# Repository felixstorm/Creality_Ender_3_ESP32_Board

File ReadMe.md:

# ESP32 RepRap Controller Board for Creality Ender 3

**Use at your own risk! This is just a personal project and work in progress, and I do not have any professional experience in this field. And although it does work nicely for me, the power supply and heaters have enough power to set your house on fire if not used correctly. Therefore be sure to think about the stuff you do yourself and respect all the necessary safety precautions!**

This is a bare minimum RepRap mainboard that I created for my own Creality Ender 3, heavily based on the work of [Simon Jouet](https://github.com/simon-jouet).  
He did a great job developing the HAL for the ESP32 for [Marlin](https://github.com/MarlinFirmware/Marlin/tree/bugfix-2.0.x/Marlin/src/HAL/HAL_ESP32) including the use of I2S and shift registers to drive the stepper drivers. I2S needs very little hardware overhead, but increases the somewhat limited number of GPIOs on the ESP32 significantly, allowing to also connect the stock Ender 3 display as well as a BLTouch and also parts cooling, control board and hotend fans independently. Additionally it provides perfect stepper timing (based on the ESP32's internal I2S clock).  
He also developed his own [ESP32 controller](https://github.com/simon-jouet/ESP32Controller) which this board is heavily based on.

This is the third iteration of the board, and although it has only been in use for a few hours yet, it does seem to work nicely in every respect. Will post updates here...

## Technical Notes
* The board is the bare minimum to help my Ender 3 to a 32 bit brain and WiFi. I use breakout boards wherever it makes sense to reduce complexity as much as possible. It is not primarly geared towards low cost, but towards little effort (although it took more of it than I hoped for in the beginning ;-) ).
* The board is through hole and single sided with a few wire bridges. This is because I am so old that I am more used to THT than SMD, because most stuff is on on breakout boards anyway and because I wanted to mill the board on my CNC.
* There is a [PDF](https://github.com/felixstorm/Creality_Ender_3_ESP32_Board/blob/master/201904_Esp32ReprapController_Schematic_and_Layout.pdf) with schematic and board layout and a [photo of my board](https://github.com/felixstorm/Creality_Ender_3_ESP32_Board/blob/master/Creality_Ender_3_ESP32_Board.jpg) available to get a quick look.
* The board is larger (100 x 160 mm) than the stock Ender 3 mainboard, so you will need (to print) a different case for it. I will probably develop one some time, put it on Thingiverse and then link it from here.
* SD card reader: I am using a microSD to regular SD extension and have the SD card reader mounted behind the display, so I used a microSD breakout board with the slot oriented inwards where I just plug in the extension cable. The board used to be 5V, but I shorted the voltage regulator with some solder to make it work with 3.3V.
* Stepper Drivers: I use TMC2208 because they are quiet and relatively cheap. Since I am not interested in any tuning here, I hard-wired it's configuration pins. In case you want to use different drivers, you might have to cut traces on these pins or change the layout.
* I have yet to make use of WiFi. My plan is to use [ESP3D](https://github.com/luc-github/ESP3D) with Marlin integrated at some point in time, but I have yet to figure out how far Luc as gotten with the integration of ESP3 into [Marlin](https://github.com/luc-github/Marlin/tree/bugfix-2.0.x).
* The board should run stock [Marlin for ESP32](https://github.com/MarlinFirmware/Marlin/tree/bugfix-2.0.x/Marlin/src/HAL/HAL_ESP32) (as my minor pull requests have all been merged now). For reference, my current personal setup including my complete configuration is available [here](https://github.com/felixstorm/Marlin/tree/Felix_Ender3_ESP32_2.0.x).
* In case you create your own board / layout, be sure to take special care of the I2S lines. The first two variants of my board also did work somehow, but the temperature readings were really, really noisy (jumping up and down wildly by 5-8 °C). It turned out that this was caused by my really poor routing of the I2S lines which injected lots of noise into VCC. The second iteration was better, but there was still more noise than I had hoped for, so I took more time for the layout of board revision r3, moved components and switched pins to separate I2S far from VCC and analog pins and to reduce the complexity of the layout, routed all power and analog lines by hand, placed a ground plane around the I2S lines and left only standard digital lines for the auto-router.
* I used [KiCad](http://www.kicad.org/) for the schematic and the board and [TopoR Lite](https://www.eremex.com/products/topor/) for auto-routing. TopoR works quite well, is available for free with some (totally acceptable) limitations and was pretty helpful as it also has a special single-sided mode, even though it took some time to get used to.
* For milling, I used [pcb2gcode](https://github.com/pcb2gcode/pcb2gcode), which also worked well for me since it allows to add safety margins easily by setting a cutter width larger than the actual cutter. It will still mill between traces that are closer together than theoretically possible with the specified cutter width (which [FlatCAM](http://flatcam.org/) unfortunately does not do), but leaves all other traces wider. And although it is command-line only, one can put all settings in a config file per project and it does dump out nice SVG files where it illustrates its calculations.

## License: MIT

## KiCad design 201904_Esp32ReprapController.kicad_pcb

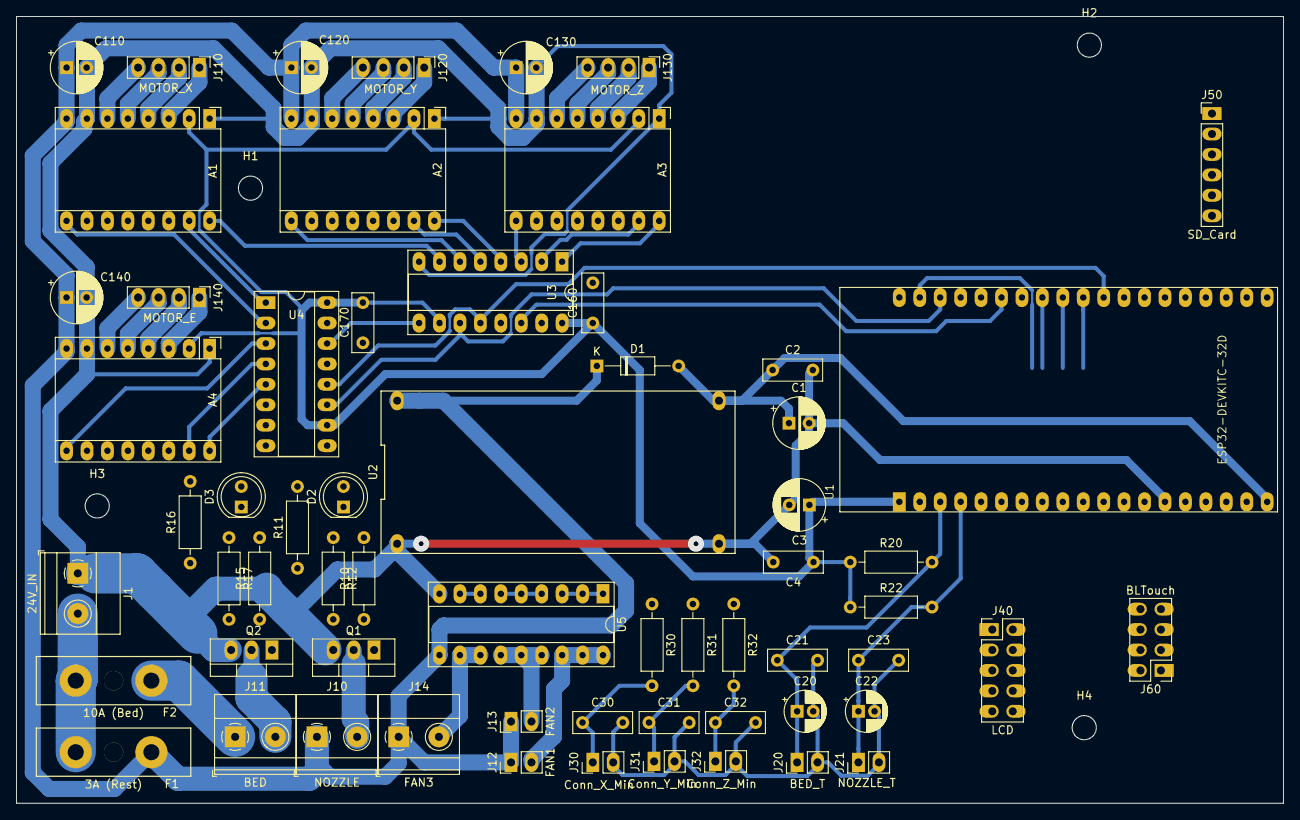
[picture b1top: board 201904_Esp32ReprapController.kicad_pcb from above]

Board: 2 copper layers, 157.5 x 97.8 mm, 66 parts (0 on the bottom side), 68 nets.

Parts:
A1: DRIVER_X; Pololu_Breakout-16_15.2x20.3mm_LongPads
A2: DRIVER_Y; Pololu_Breakout-16_15.2x20.3mm_LongPads
A3: DRIVER_Z; Pololu_Breakout-16_15.2x20.3mm_LongPads
A4: DRIVER_E; Pololu_Breakout-16_15.2x20.3mm_LongPads
C1, C3, C110, C120, C130, C140: 100uF; CP_Radial_D6.3mm_P2.50mm
C2, C4, C21, C23, C30, C31, C32, C160, C170: 0.1uF; C_Rect_L7.2mm_W2.5mm_P5.00mm_FKS2_FKP2_MKS2_MKP2
C20, C22: 4.7uF; CP_Radial_D5.0mm_P2.00mm
D1: 1N5819; D_DO-35_SOD27_P10.16mm_Horizontal
D2: LED_NOZ; LED_D5.0mm
D3: LED_BED; LED_D5.0mm
F1: 3A (Rest); Fuse_ESKA_380.000
F2: 10A (Bed); Fuse_ESKA_380.000
H1, H2, H3, H4: MountingHole; MountingHole_3mm
J1: 24V_IN; TerminalBlock_ScrewTerminal_1x02_P5.00mm_Horizontal
J10: NOZZLE; TerminalBlock_ScrewTerminal_1x02_P5.00mm_Horizontal
J11: BED; TerminalBlock_ScrewTerminal_1x02_P5.00mm_Horizontal
J12: FAN1; PinHeader_1x02_P2.54mm_Vertical_LongPads
J13: FAN2; PinHeader_1x02_P2.54mm_Vertical_LongPads
J14: FAN3; TerminalBlock_ScrewTerminal_1x02_P5.00mm_Horizontal
J20: BED_T; PinHeader_1x02_P2.54mm_Vertical_LongPads
J21: NOZZLE_T; PinHeader_1x02_P2.54mm_Vertical_LongPads
J30: Conn_X_Min; PinHeader_1x02_P2.54mm_Vertical_LongPads
J31: Conn_Y_Min; PinHeader_1x02_P2.54mm_Vertical_LongPads
J32: Conn_Z_Min; PinHeader_1x02_P2.54mm_Vertical_LongPads
J40: LCD; PinHeader_2x05_P2.54mm_Vertical_LongPads
J50: SD_Card; PinHeader_1x06_P2.54mm_Vertical_LongPads
J60: BLTouch; PinHeader_2x04_P2.54mm_Vertical_LongPads
J110: MOTOR_X; PinHeader_1x04_P2.54mm_Vertical_LongPads
J120: MOTOR_Y; PinHeader_1x04_P2.54mm_Vertical_LongPads
J130: MOTOR_Z; PinHeader_1x04_P2.54mm_Vertical_LongPads
J140: MOTOR_E; PinHeader_1x04_P2.54mm_Vertical_LongPads
Q1: IRLZ44N; TO-220-3_Vertical_LongPads
Q2: IRLB8743; TO-220-3_Vertical_LongPads
R10, R15: 10; R_Axial_DIN0207_L6.3mm_D2.5mm_P10.16mm_Horizontal
R11, R16: 100k; R_Axial_DIN0207_L6.3mm_D2.5mm_P10.16mm_Horizontal
R12, R17: 2.2k; R_Axial_DIN0207_L6.3mm_D2.5mm_P10.16mm_Horizontal
R20, R22: 4.7k; R_Axial_DIN0207_L6.3mm_D2.5mm_P10.16mm_Horizontal
R30, R31, R32: 10k; R_Axial_DIN0207_L6.3mm_D2.5mm_P10.16mm_Horizontal
U1: ESP32-DEVKITC-32D; MODULE_ESP32-DEVKITC-32D_LongPads
U2: DcStepDown_LM2596; Module_LM2596_DC-DC
U3, U4: 74HC595; DIP-16_W7.62mm_Socket_LongPads
U5: ULN2803A; DIP-18_W7.62mm_Socket_LongPads

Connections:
+5V: C1.1, C2.1, D1.2, J40.10, J60.2, U1.19, U2.3
+24V: A1.8, A2.8, A3.8, A4.8, C110.1, C120.1, C130.1, C140.1, D1.1, D2.2, D3.2, F1.1, J10.1, J12.1, J13.1, J14.1, U2.1, U5.10
+24V2: F2.1, J11.1
/I36_T_BED: C20.1, C21.1, J20.1, R20.2, U1.3
/I39_T_NOZ: C22.1, C23.1, J21.1, R22.2, U1.4
/IO17_I2S_WS: U1.30, U3.12, U4.12
/IO21_I2S_BCK: U1.22, U3.11, U4.11
/IO22_I2S_DATA: U1.25, U3.14
/IOx_BED: R15.2, R16.2, U1.34
/IOx_BTN_EN1: J40.3, U1.8
/IOx_BTN_EN2: J40.5, U1.9
/IOx_BTN_ENC: J40.2, U1.10
/IOx_FAN1: U1.15, U5.1, U5.2, U5.3
/IOx_LCD_D4: J40.6, U1.11
/IOx_LCD_EN: J40.8, U1.13
/IOx_LCD_RS: J40.7, U1.12
/IOx_NOZZLE: R10.2, R11.2, U1.32
/IOx_SERVO: J60.8, U1.35
/IOx_X_MIN: C30.1, J30.1, R30.2, U1.5
/IOx_Y_MIN: C31.1, J31.1, R31.2, U1.6
/IOx_Z_MIN: C32.1, J32.1, R32.2, U1.7
/PWR_IN: F1.2, F2.2, J1.2
/Q129_Z_DIR: A3.16, U3.1
/Q130_Z_STEP: A3.15, U3.2
/Q131_Z_EN: A3.9, U3.3
/Q132_Y_DIR: A2.16, U3.4
/Q133_Y_STEP: A2.15, U3.5
/Q134_Y_EN: A2.9, U3.6
/Q135_X_DIR: A1.16, U3.7
/Q137_X_STEP: A1.15, U4.1
/Q138_X_EN: A1.9, U4.2
/Q139_E_EN: A4.9, U4.3
/Q140_E_STEP: A4.15, U4.4
/Q141_E_DIR: A4.16, U4.5
/Q142_FAN2: U4.6, U5.4, U5.5, U5.6
/Q143_FAN3: U4.7, U5.7, U5.8
/SD_CS: J50.6, U1.29
/SD_MISO: J50.3, U1.27
/SD_MOSI: J50.4, U1.21
/SD_SCK: J50.5, U1.28
GND: A1.1, A1.7, A2.1, A2.7, A3.1, A3.7, A4.1, A4.7, C1.2, C2.2, C3.2, C4.2, C20.2, C21.2, C22.2, C23.2, C30.2, C31.2, C32.2, C110.2, C120.2, C130.2, C140.2, C160.2, C170.2, J1.1, J20.2, J21.2, J30.2, J31.2, J32.2, J40.9, J50.1, J60.6, Q1.3, Q2.3, R11.1, R16.1, U1.14, U1.20, U1.26, U2.2, U2.4, U3.8, U3.13, U4.8, U4.13, U5.9
unnamed: A1.3, J110.1
unnamed: A1.4, J110.2
unnamed: A1.5, J110.3
unnamed: A1.6, J110.4
unnamed: A2.3, J120.1
unnamed: A2.4, J120.2
unnamed: A2.5, J120.3
unnamed: A2.6, J120.4
unnamed: A3.3, J130.1
unnamed: A3.4, J130.2
unnamed: A3.5, J130.3
unnamed: A3.6, J130.4
unnamed: A4.3, J140.1
unnamed: A4.4, J140.2
unnamed: A4.5, J140.3
unnamed: A4.6, J140.4
unnamed: D2.1, R12.1
unnamed: D3.1, R17.1
unnamed: J10.2, Q1.2, R12.2
unnamed: J11.2, Q2.2, R17.2
unnamed: J12.2, U5.16, U5.17, U5.18
unnamed: J13.2, U5.13, U5.14, U5.15
unnamed: J14.2, U5.11, U5.12
unnamed: Q1.1, R10.1
unnamed: Q2.1, R15.1
unnamed: U3.9, U4.14
VCC: A1.2, A1.10, A1.11, A2.2, A2.10, A2.11, A3.2, A3.10, A3.11, A4.2, A4.10, A4.11, C3.1, C4.1, C160.1, C170.1, J50.2, R20.1, R22.1, R30.1, R31.1, R32.1, U1.1, U3.10, U3.16, U4.10, U4.16

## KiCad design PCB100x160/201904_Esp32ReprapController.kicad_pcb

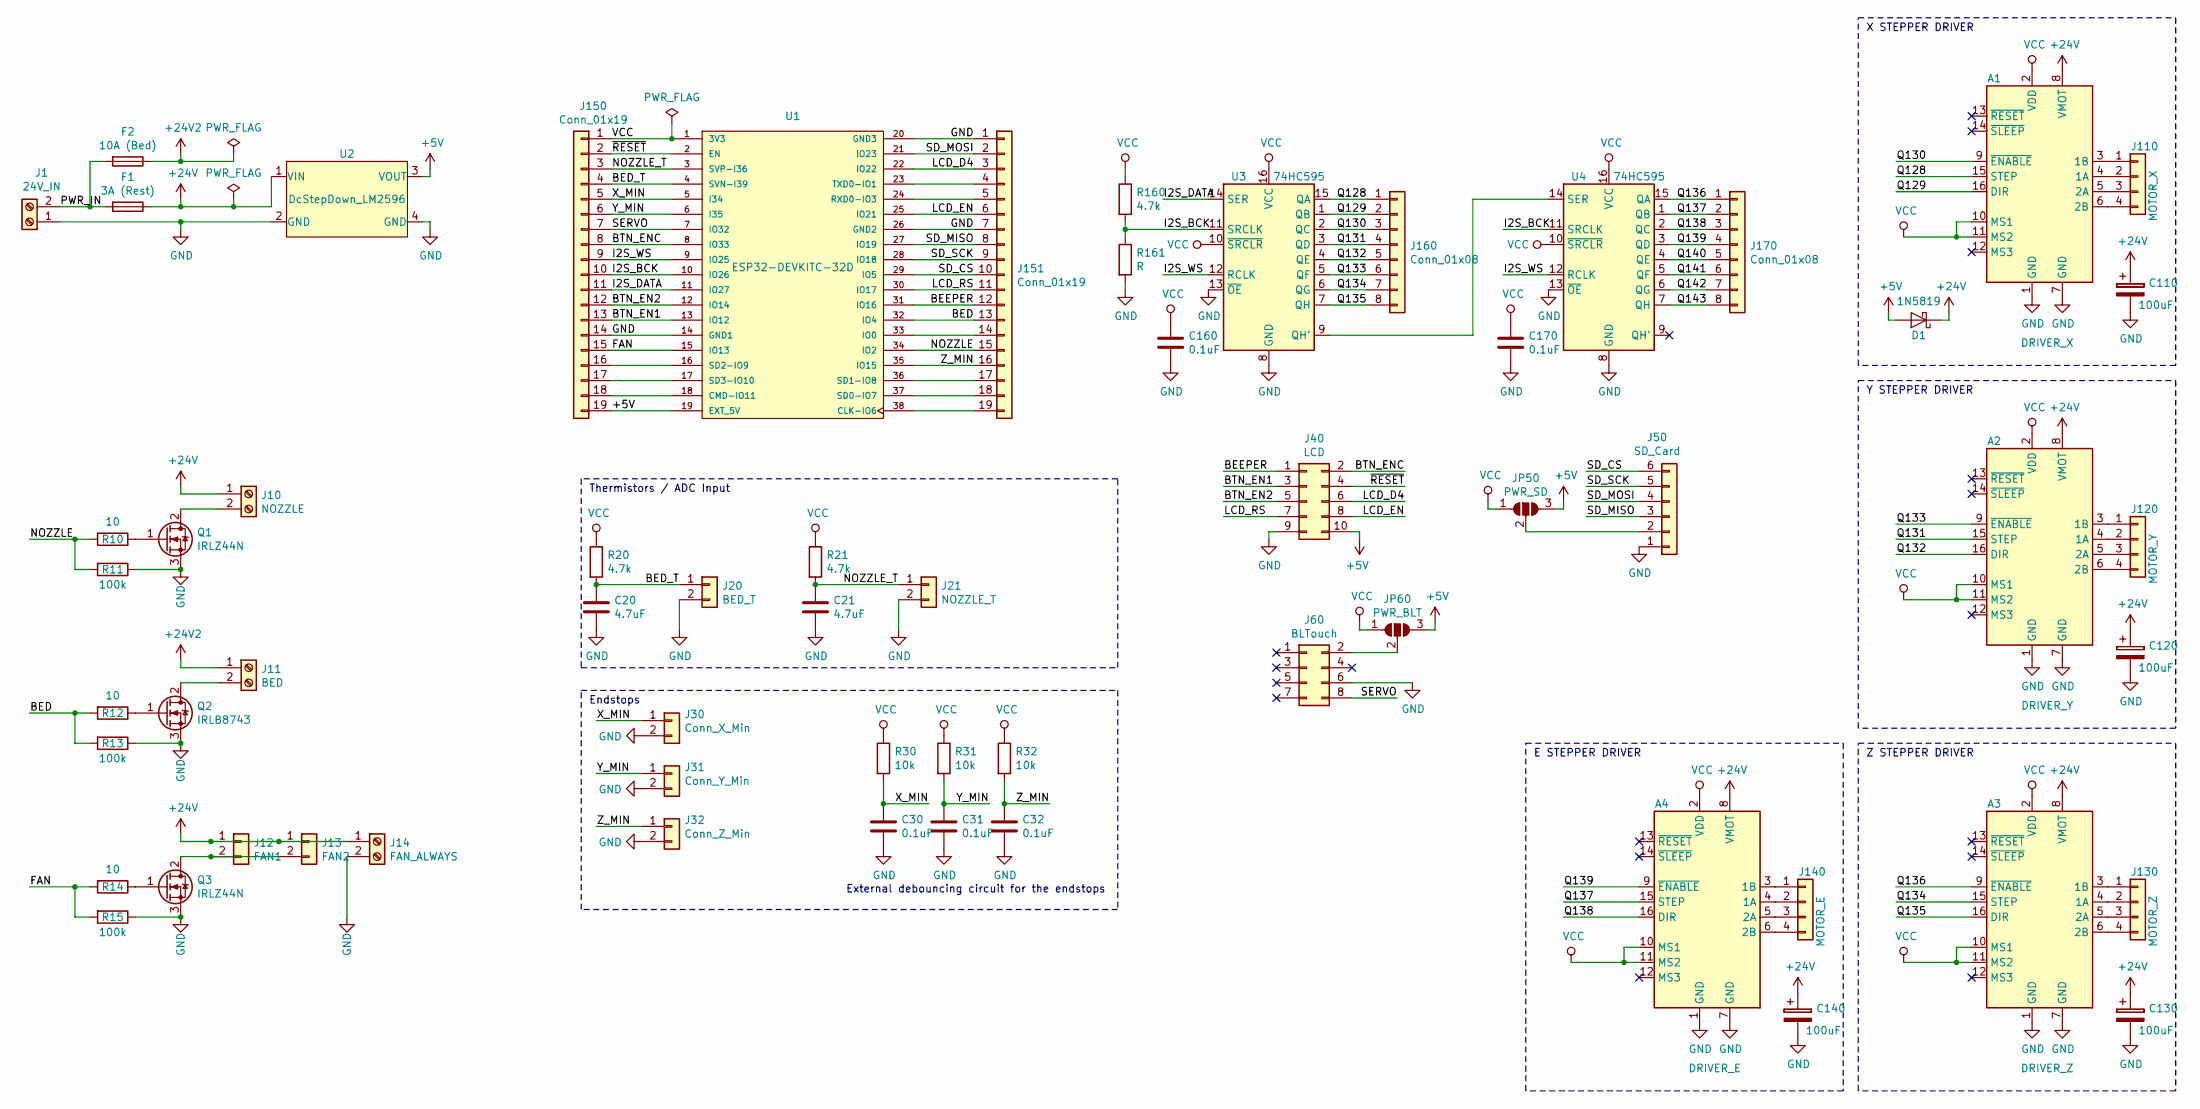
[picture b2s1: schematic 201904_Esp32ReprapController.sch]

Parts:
A1: DRIVER_X; Pololu_Breakout-16_15.2x20.3mm_LongPads
A2: DRIVER_Y; Pololu_Breakout-16_15.2x20.3mm_LongPads
A3: DRIVER_Z; Pololu_Breakout-16_15.2x20.3mm_LongPads
A4: DRIVER_E; Pololu_Breakout-16_15.2x20.3mm_LongPads
C20, C21: 4.7uF; CP_Radial_D5.0mm_P2.00mm
C30, C31, C32, C160, C170: 0.1uF; C_Rect_L7.2mm_W2.5mm_P5.00mm_FKS2_FKP2_MKS2_MKP2
C110, C120, C130, C140: 100uF; CP_Radial_D6.3mm_P2.50mm
D1: 1N5819; D_DO-35_SOD27_P10.16mm_Horizontal
F1: 3A (Rest); Fuse_ESKA_380.000
F2: 10A (Bed); Fuse_ESKA_380.000
J1: 24V_IN; TerminalBlock_ScrewTerminal_1x02_P5.00mm_Horizontal
J10: NOZZLE; TerminalBlock_ScrewTerminal_1x02_P5.00mm_Horizontal
J11: BED; TerminalBlock_ScrewTerminal_1x02_P5.00mm_Horizontal
J12: FAN1; PinHeader_1x02_P2.54mm_Vertical_LongPads
J13: FAN2; PinHeader_1x02_P2.54mm_Vertical_LongPads
J14: FAN_ALWAYS; TerminalBlock_ScrewTerminal_1x02_P5.00mm_Horizontal
J20: BED_T; PinHeader_1x02_P2.54mm_Vertical_LongPads
J21: NOZZLE_T; PinHeader_1x02_P2.54mm_Vertical_LongPads
J30: Conn_X_Min; PinHeader_1x02_P2.54mm_Vertical_LongPads
J31: Conn_Y_Min; PinHeader_1x02_P2.54mm_Vertical_LongPads
J32: Conn_Z_Min; PinHeader_1x02_P2.54mm_Vertical_LongPads
J40: LCD; PinHeader_2x05_P2.54mm_Vertical_LongPads
J50: SD_Card; PinHeader_1x06_P2.54mm_Vertical_LongPads
J60: BLTouch; PinHeader_2x04_P2.54mm_Vertical_LongPads
J110: MOTOR_X; PinHeader_1x04_P2.54mm_Vertical_LongPads
J120: MOTOR_Y; PinHeader_1x04_P2.54mm_Vertical_LongPads
J130: MOTOR_Z; PinHeader_1x04_P2.54mm_Vertical_LongPads
J140: MOTOR_E; PinHeader_1x04_P2.54mm_Vertical_LongPads
J150, J151: Conn_01x19; PinHeader_1x19_P2.54mm_Vertical_LongPads
J160, J170: Conn_01x08; PinHeader_1x08_P2.54mm_Vertical_LongPads
JP50: PWR_SD; SolderJumper-3_P1.3mm_Open_Pad1.0x1.5mm_NumberLabels_Bottom
JP60: PWR_BLT; SolderJumper-3_P1.3mm_Open_Pad1.0x1.5mm_NumberLabels_Bottom
Q1, Q3: IRLZ44N; TO-220-3_Vertical_LongPads
Q2: IRLB8743; TO-220-3_Vertical_LongPads
R10, R12, R14: 10; R_Axial_DIN0207_L6.3mm_D2.5mm_P10.16mm_Horizontal
R11, R13, R15: 100k; R_Axial_DIN0207_L6.3mm_D2.5mm_P10.16mm_Horizontal
R20, R21, R160: 4.7k; R_Axial_DIN0207_L6.3mm_D2.5mm_P10.16mm_Horizontal
R30, R31, R32: 10k; R_Axial_DIN0207_L6.3mm_D2.5mm_P10.16mm_Horizontal
R161: R; R_Axial_DIN0207_L6.3mm_D2.5mm_P10.16mm_Horizontal
U1: ESP32-DEVKITC-32D; MODULE_ESP32-DEVKITC-32D_LongPads
U2: DcStepDown_LM2596; Module_LM2596_DC-DC
U3, U4: 74HC595; DIP-16_W7.62mm_Socket_LongPads

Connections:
+5V: D1.2 (A), J40.10, J150.19, JP50.3 (B), JP60.3 (B), U1.19 (EXT_5V), U2.3 (VOUT)
+24V: A1.8 (VMOT), A2.8 (VMOT), A3.8 (VMOT), A4.8 (VMOT), C110.1, C120.1, C130.1, C140.1, D1.1 (K), F1.1, J10.1, J12.1, J13.1, J14.1, U2.1 (VIN)
+24V2: F2.1, J11.1
/BED: J151.13, R12.2, R13.2, U1.32 (IO4)
/BED_T: C20.1, J20.1, J150.4, R20.2, U1.4 (SVN-I39)
/BEEPER: J40.1, J151.12, U1.31 (IO16)
/BTN_EN1: J40.3, J150.13, U1.13 (IO12)
/BTN_EN2: J40.5, J150.12, U1.12 (IO14)
/BTN_ENC: J40.2, J150.8, U1.8 (IO33)
/FAN: J150.15, R14.2, R15.2, U1.15 (IO13)
/I2S_BCK: J150.10, R160.2, R161.1, U1.10 (IO26), U3.11 (SRCLK), U4.11 (SRCLK)
/I2S_DATA: J150.11, U1.11 (IO27), U3.14 (SER)
/I2S_WS: J150.9, U1.9 (IO25), U3.12 (RCLK), U4.12 (RCLK)
/LCD_D4: J40.6, J151.3, U1.22 (IO22)
/LCD_EN: J40.8, J151.6, U1.25 (IO21)
/LCD_RS: J40.7, J151.11, U1.30 (IO17)
/NOZZLE: J151.15, R10.2, R11.2, U1.34 (IO2)
/NOZZLE_T: C21.1, J21.1, J150.3, R21.2, U1.3 (SVP-I36)
/PWR_IN: F1.2, F2.2, J1.2
/Q128: A1.15 (STEP), J160.1, U3.15 (QA)
/Q129: A1.16 (DIR), J160.2, U3.1 (QB)
/Q130: A1.9 (~ENABLE), J160.3, U3.2 (QC)
/Q131: A2.15 (STEP), J160.4, U3.3 (QD)
/Q132: A2.16 (DIR), J160.5, U3.4 (QE)
/Q133: A2.9 (~ENABLE), J160.6, U3.5 (QF)
/Q134: A3.15 (STEP), J160.7, U3.6 (QG)
/Q135: A3.16 (DIR), J160.8, U3.7 (QH)
/Q136: A3.9 (~ENABLE), J170.1, U4.15 (QA)
/Q137: A4.15 (STEP), J170.2, U4.1 (QB)
/Q138: A4.16 (DIR), J170.3, U4.2 (QC)
/Q139: A4.9 (~ENABLE), J170.4, U4.3 (QD)
/Q140: J170.5, U4.4 (QE)
/Q141: J170.6, U4.5 (QF)
/Q142: J170.7, U4.6 (QG)
/Q143: J170.8, U4.7 (QH)
/SD_CS: J50.6, J151.10, U1.29 (IO5)
/SD_MISO: J50.3, J151.8, U1.27 (IO19)
/SD_MOSI: J50.4, J151.2, U1.21 (IO23)
/SD_SCK: J50.5, J151.9, U1.28 (IO18)
/SERVO: J60.8, J150.7, U1.7 (IO32)
/X_MIN: C30.1, J30.1, J150.5, R30.2, U1.5 (I34)
/Y_MIN: C31.1, J31.1, J150.6, R31.2, U1.6 (I35)
/Z_MIN: C32.1, J32.1, J151.16, R32.2, U1.35 (IO15)
/~RESET: J40.4, J150.2, U1.2 (EN)
GND: A1.1 (GND), A1.7 (GND), A2.1 (GND), A2.7 (GND), A3.1 (GND), A3.7 (GND), A4.1 (GND), A4.7 (GND), C20.2, C21.2, C30.2, C31.2, C32.2, C110.2, C120.2, C130.2, C140.2, C160.2, C170.2, J1.1, J14.2, J20.2, J21.2, J30.2, J31.2, J32.2, J40.9, J50.1, J60.6, J150.14, J151.1, J151.7, Q1.3 (S), Q2.3 (S), Q3.3 (S), R11.1, R13.1, R15.1, R161.2, U1.14 (GND1), U1.20 (GND3), U1.26 (GND2), U2.2 (GND), U2.4 (GND), U3.8 (GND), U3.13 (~OE), U4.8 (GND), U4.13 (~OE)
unnamed: A1.3 (1B), J110.1
unnamed: A1.4 (1A), J110.2
unnamed: A1.5 (2A), J110.3
unnamed: A1.6 (2B), J110.4
unnamed: A2.3 (1B), J120.1
unnamed: A2.4 (1A), J120.2
unnamed: A2.5 (2A), J120.3
unnamed: A2.6 (2B), J120.4
unnamed: A3.3 (1B), J130.1
unnamed: A3.4 (1A), J130.2
unnamed: A3.5 (2A), J130.3
unnamed: A3.6 (2B), J130.4
unnamed: A4.3 (1B), J140.1
unnamed: A4.4 (1A), J140.2
unnamed: A4.5 (2A), J140.3
unnamed: A4.6 (2B), J140.4
unnamed: J10.2, Q1.2 (D)
unnamed: J11.2, Q2.2 (D)
unnamed: J12.2, J13.2, Q3.2 (D)
unnamed: J50.2, JP50.2 (C)
unnamed: J60.2, JP60.2 (C)
unnamed: J150.16, U1.16 (SD2-IO9)
unnamed: J150.17, U1.17 (SD3-IO10)
unnamed: J150.18, U1.18 (CMD-IO11)
unnamed: J151.4, U1.23 (TXD0-IO1)
unnamed: J151.5, U1.24 (RXD0-IO3)
unnamed: J151.14, U1.33 (IO0)
unnamed: J151.17, U1.36 (SD1-IO8)
unnamed: J151.18, U1.37 (SD0-IO7)
unnamed: J151.19, U1.38 (CLK-IO6)
unnamed: Q1.1 (G), R10.1
unnamed: Q2.1 (G), R12.1
unnamed: Q3.1 (G), R14.1
unnamed: U3.9 (QH'), U4.14 (SER)
VCC: A1.2 (VDD), A1.10 (MS1), A1.11 (MS2), A2.2 (VDD), A2.10 (MS1), A2.11 (MS2), A3.2 (VDD), A3.10 (MS1), A3.11 (MS2), A4.2 (VDD), A4.10 (MS1), A4.11 (MS2), C160.1, C170.1, J150.1, JP50.1 (A), JP60.1 (A), R20.1, R21.1, R30.1, R31.1, R32.1, R160.1, U1.1 (3V3), U3.10 (~SRCLR), U3.16 (VCC), U4.10 (~SRCLR), U4.16 (VCC)

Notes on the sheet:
X STEPPER DRIVER
Thermistors / ADC Input
Endstops
External debouncing circuit for the endstops
Y STEPPER DRIVER
Z STEPPER DRIVER
E STEPPER DRIVER

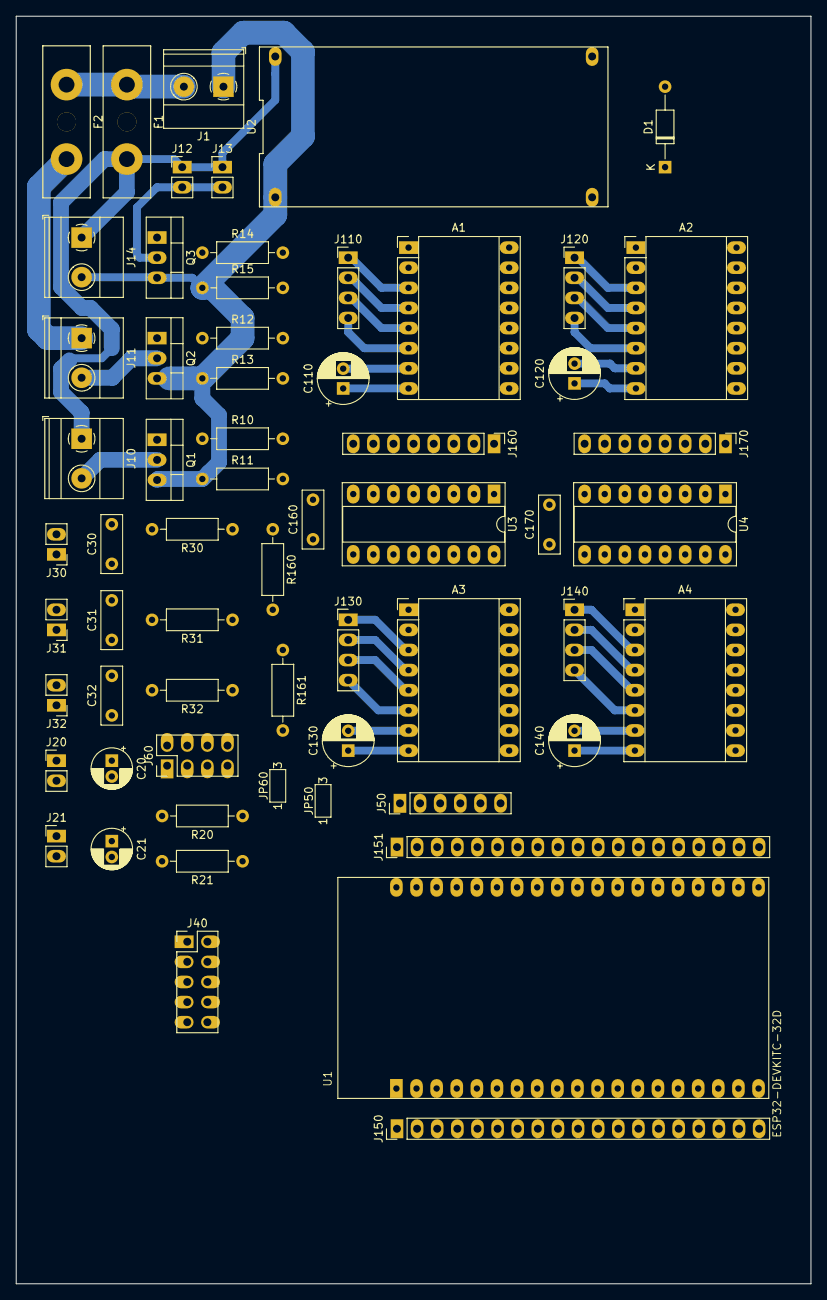
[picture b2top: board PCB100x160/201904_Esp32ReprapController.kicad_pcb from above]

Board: 2 copper layers, 100.3 x 160.0 mm, 62 parts (0 on the bottom side), 80 nets.

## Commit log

2019-05-12 board r1 (milled and built 2019-05)
2019-06-06 board r2 (never built)
2019-06-06 remove older stuff
2019-06-06 board r3 (milled and built 2019-06)
2019-06-07 cosmetics
2019-06-08 add ReadMe.md
2019-06-09 add photo
2021-11-08 Update ReadMe.md
    https://forum.kicad.info/t/warning-avoid-all-links-to-kicad-pcb-org-use-kicad-org/31521
